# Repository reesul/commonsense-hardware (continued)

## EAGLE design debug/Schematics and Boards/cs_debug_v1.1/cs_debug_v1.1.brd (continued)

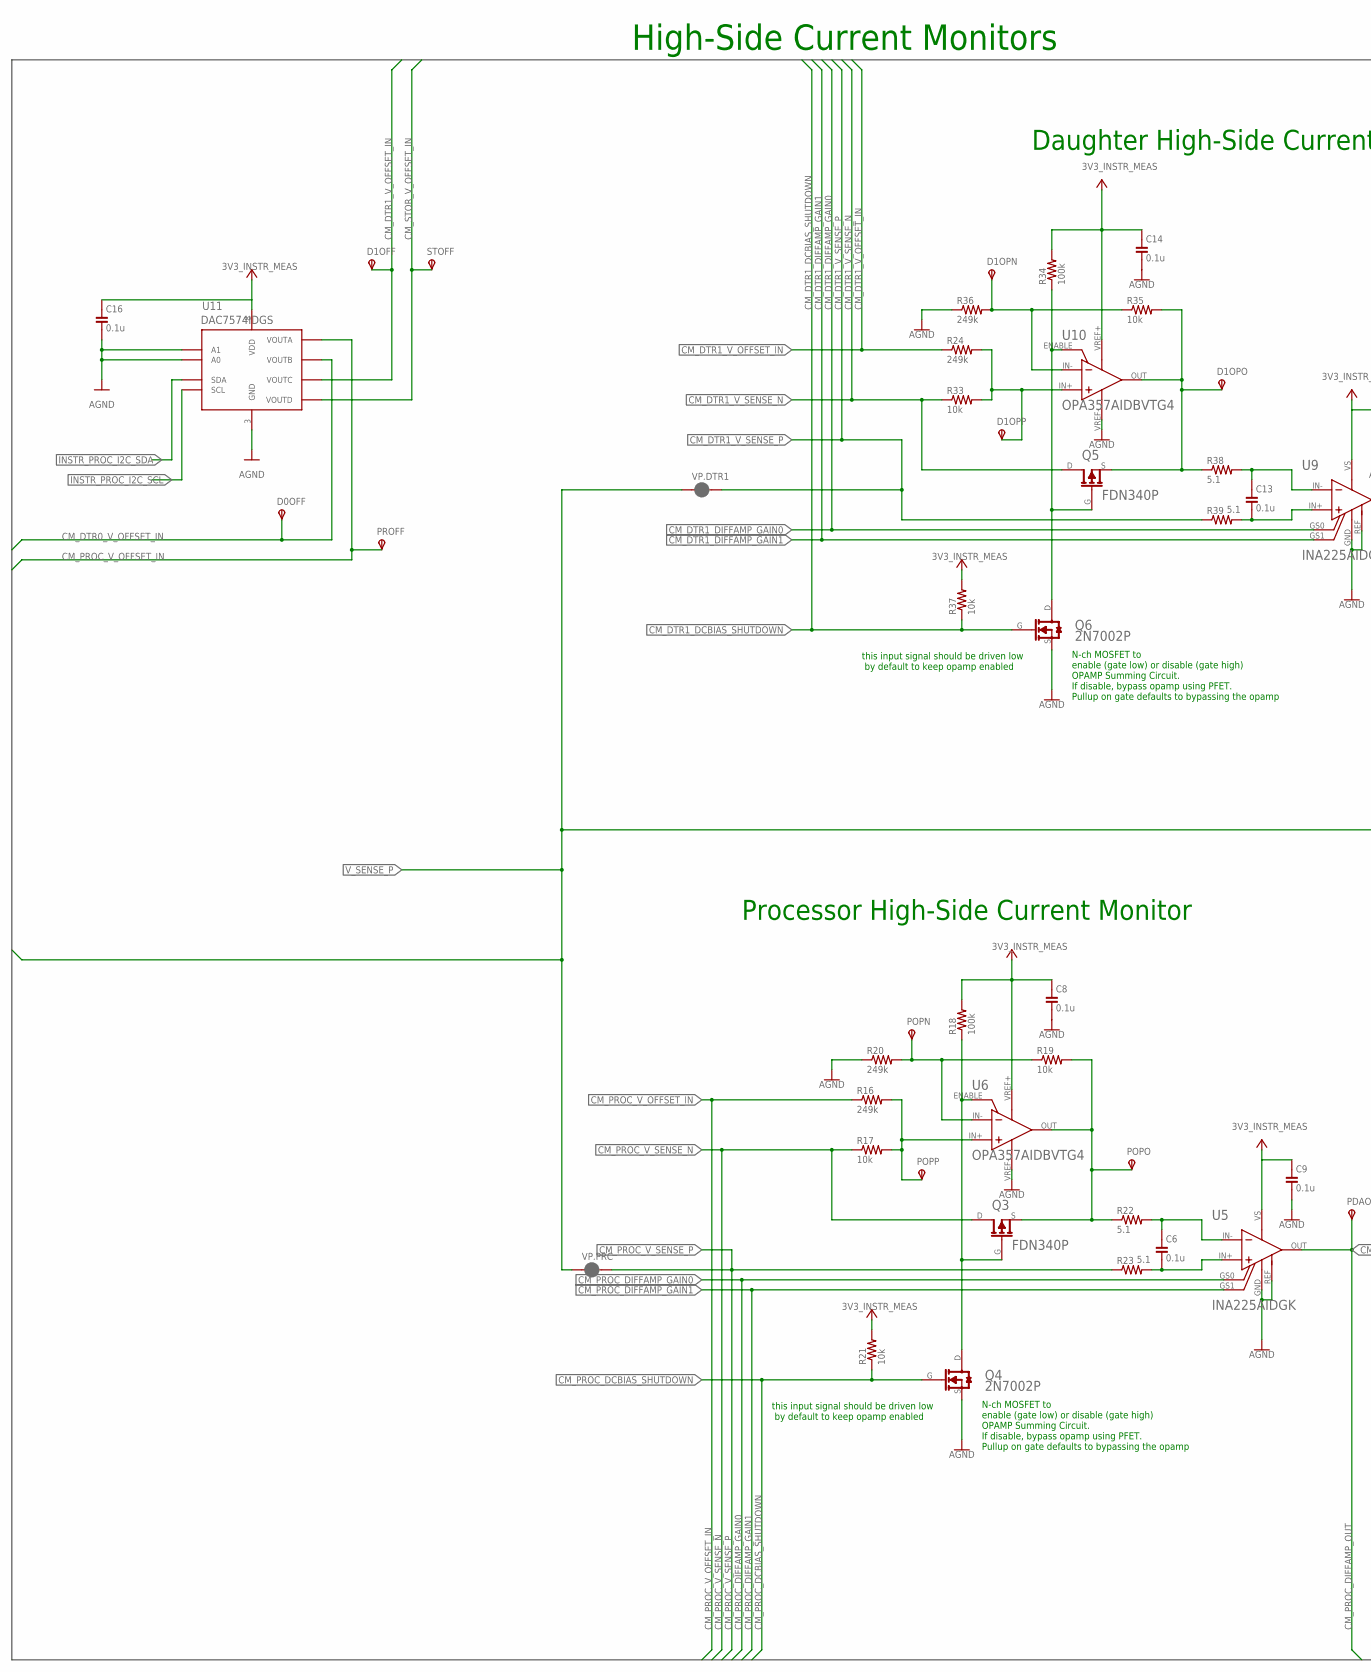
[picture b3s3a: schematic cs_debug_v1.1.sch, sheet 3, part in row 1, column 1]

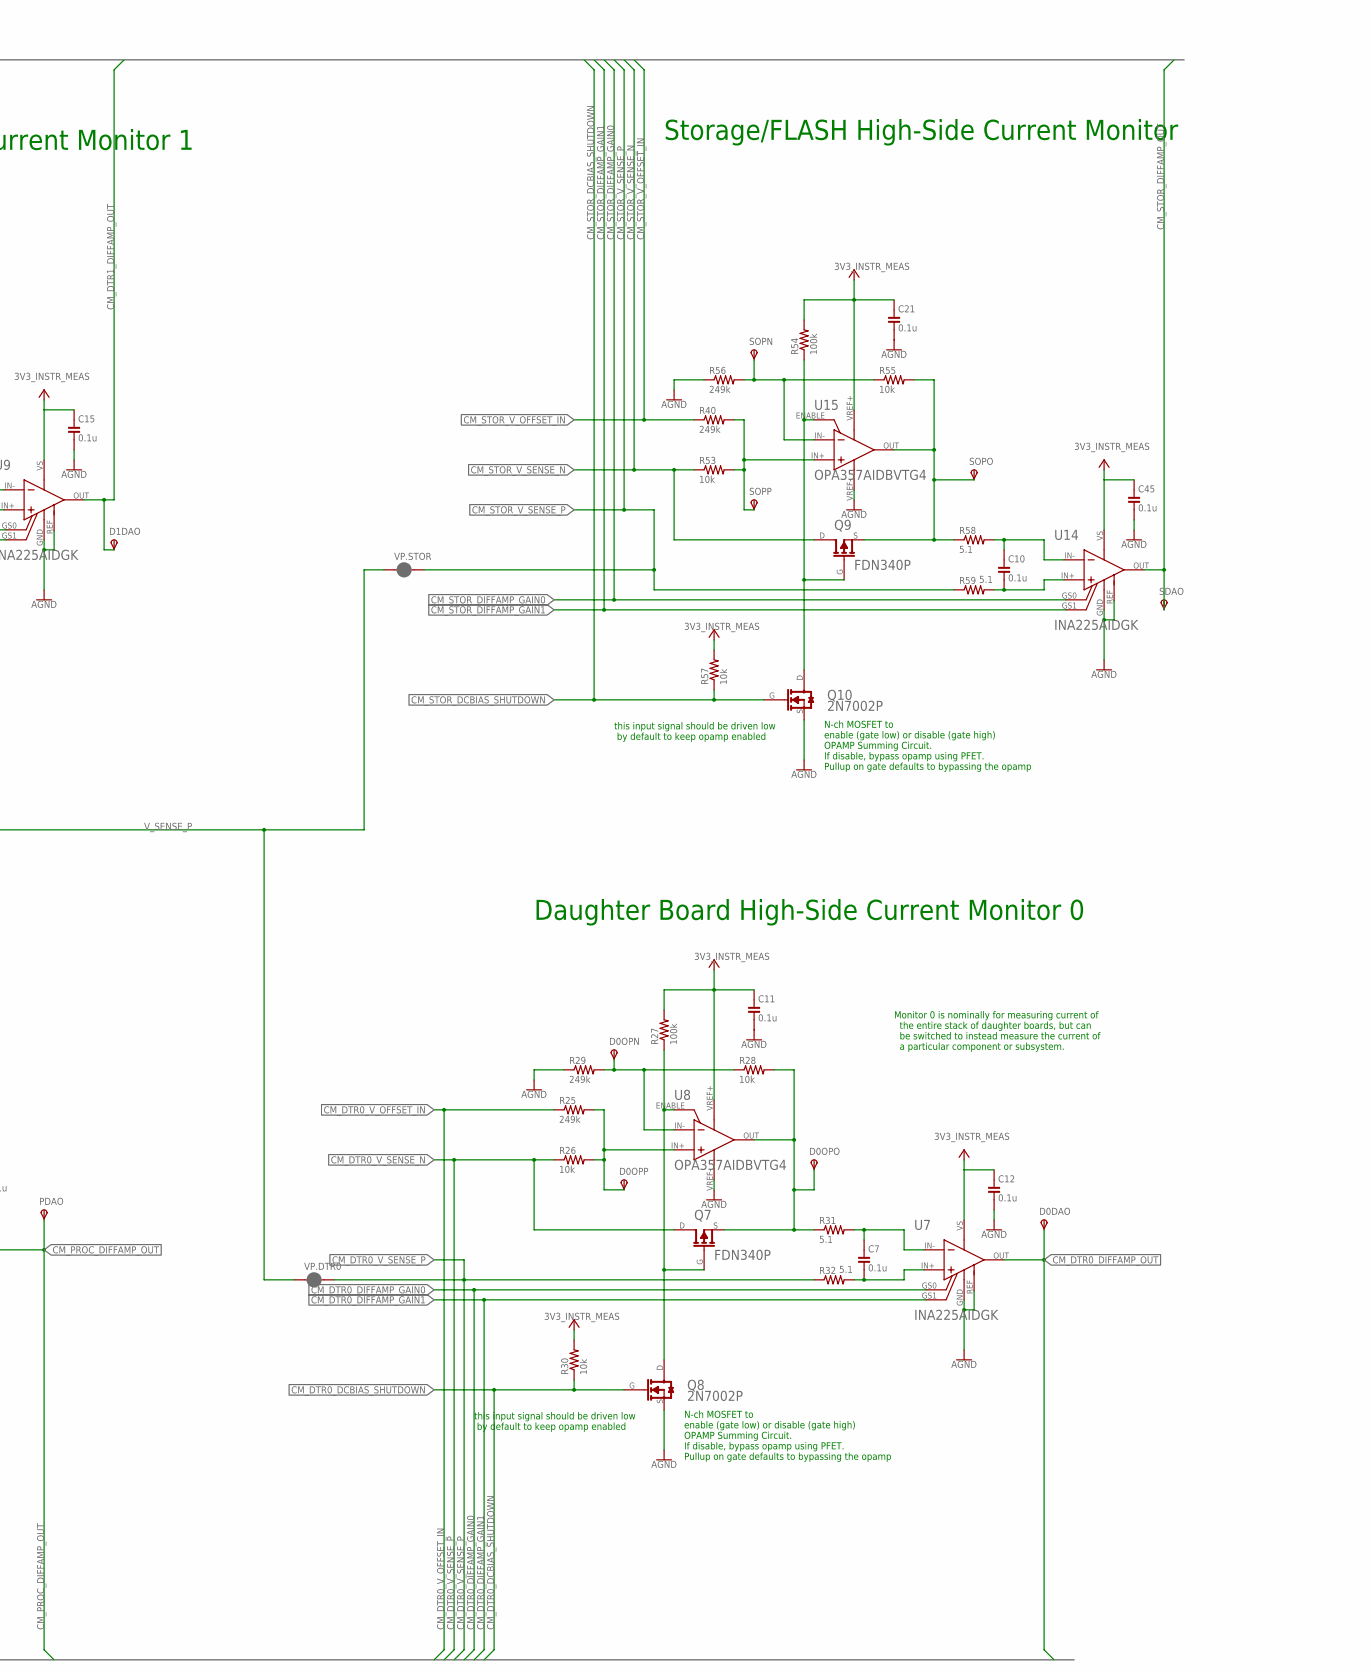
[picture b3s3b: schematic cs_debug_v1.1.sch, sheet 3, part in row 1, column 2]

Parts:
C6, C7, C10, C13: 0.1u; C0402; VOLTAGE 10V; MPN C0402C104K4RAC7411
C8, C9, C11, C12, C14, C15, C16, C21, C45: 0.1u; C0402; VOLTAGE 10V; MPN C0402C104K8RACTU
D0DAO, D0OFF, D0OPN, D0OPO, D0OPP, D1DAO, D1OFF, D1OPN, D1OPO, D1OPP: TPSTP10SQ; TP10SQ
PDAO: TPSTP10SQ; TP10SQ
POPN: TPSTP10SQ; TP10SQ
POPO: TPSTP10SQ; TP10SQ
POPP: TPSTP10SQ; TP10SQ
PROFF: TPSTP10SQ; TP10SQ
Q3, Q5, Q7, Q9: FDN340P; SOT23-3_FDN340P; PART_NO FDN340P
Q4, Q6, Q8, Q10: 2N7002P; SOT23-3_2N7002P; MPN 2N7002P,215
R16, R20, R24, R25, R29, R36, R40, R56: 249k; R0603; MPN ERA-3AEB2493V
R17, R19, R26, R28, R33, R35, R53, R55: 10k; R0402; MPN ERA-2AEB103X
R18, R27, R34, R54: 100k; R0402; MPN ERJ-2RKF1003X
R21, R30, R37, R57: 10k; R0402; MPN ERJ-2RKF1002X
R22, R23, R31, R32, R38, R39, R58: 5.1; R0603; MPN ERJ-U03F5R10V
R59: 5.1; R0603; MPN ERJ-3BQF5R1V
SDAO: TPSTP10SQ; TP10SQ
SOPN: TPSTP10SQ; TP10SQ
SOPO: TPSTP10SQ; TP10SQ
SOPP: TPSTP10SQ; TP10SQ
STOFF: TPSTP10SQ; TP10SQ
U5, U7, U9, U14: INA225AIDGK; DGK-MSOP8_INA225; MPN INA225AIDGKT
U6, U8, U10, U15: OPA357AIDBVTG4; PART_NO OPA357AIDBVTG4
U11: DAC7574IDGS; DGS10; MPN DAC7574IDGS
VP.DTR0, VP.DTR1, VP.PRC, VP.STOR: JUMPER-SMT_2_NC_PASTE_NO-SILK; SMT-JUMPER_2_NC_PASTE_NO-SILK

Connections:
3V3_INSTR_MEAS: C8.1, C9.1, C11.1, C12.1, C14.1, C15.1, C16.1, C21.1, C45.1, R18.2, R21.2, R27.2, R30.2, R34.2, R37.2, R54.2, R57.2, U5.VS (V+), U6.VREF+ (V+), U7.VS (V+), U8.VREF+ (V+), U9.VS (V+), U10.VREF+ (V+), U11.8 (VDD), U14.VS (V+), U15.VREF+ (V+); also elsewhere on the board
AGND: C8.2, C9.2, C11.2, C12.2, C14.2, C15.2, C16.2, C21.2, C45.2, Q4.S (SOURCE), Q6.S (SOURCE), Q8.S (SOURCE), Q10.S (SOURCE), R20.1, R29.1, R36.1, R56.1, U5.GND (V-), U5.REF, U6.VREF- (V-), U7.GND (V-), U7.REF, U8.VREF- (V-), U9.GND (V-), U9.REF, U10.VREF- (V-), U11.3 (GND), U11.9 (A0), U11.10 (A1), U14.GND (V-), U14.REF, U15.VREF- (V-); also elsewhere on the board
CM_DIFFAMP_N4: C6.1, R22.2, U5.IN-
CM_DIFFAMP_P4: C6.2, R23.2, U5.IN+
CM_DTR0_DCBIAS_SHUTDOWN: Q8.G (GATE), R30.1; also elsewhere on the board
CM_DTR0_DIFFAMP_GAIN0: U7.GS0; also elsewhere on the board
CM_DTR0_DIFFAMP_GAIN1: U7.GS1; also elsewhere on the board
CM_DTR0_DIFFAMP_N: C7.1, R31.2, U7.IN-
CM_DTR0_DIFFAMP_OUT: D0DAO.TP, U7.OUT; also elsewhere on the board
CM_DTR0_DIFFAMP_P3: C7.2, R32.2, U7.IN+
CM_DTR0_OPAMP_ENABLE: Q7.G, Q8.D (DRAIN), R27.1, U8.ENABLE
CM_DTR0_OPAMP_N: D0OPN.TP, R28.1, R29.2, U8.IN-
CM_DTR0_OPAMP_OUT: D0OPO.TP, Q7.S, R28.2, R31.1, U8.OUT
CM_DTR0_V_OFFSET_IN: D0OFF.TP, R25.1, U11.2 (VOUTB)
CM_DTR0_V_SENSE_N: Q7.D, R26.1; also elsewhere on the board
CM_DTR0_V_SENSE_P: R32.1, VP.DTR0.2
CM_DTR1_DCBIAS_SHUTDOWN: Q6.G (GATE), R37.1; also elsewhere on the board
CM_DTR1_DIFFAMP_GAIN0: U9.GS0; also elsewhere on the board
CM_DTR1_DIFFAMP_GAIN1: U9.GS1; also elsewhere on the board
CM_DTR1_DIFFAMP_N: C13.1, R38.2, U9.IN-
CM_DTR1_DIFFAMP_OUT: D1DAO.TP, U9.OUT; also elsewhere on the board
CM_DTR1_DIFFAMP_P: C13.2, R39.2, U9.IN+
CM_DTR1_OPAMP_N: D1OPN.TP, R35.1, R36.2, U10.IN-
CM_DTR1_OPAMP_OUT: D1OPO.TP, Q5.S, R35.2, R38.1, U10.OUT
CM_DTR1_OPAMP_P: D1OPP.TP, R24.2, R33.2, U10.IN+
CM_DTR1_V_OFFSET_IN: D1OFF.TP, R24.1, U11.4 (VOUTC)
CM_DTR1_V_SENSE_N: Q5.D, R33.1; also elsewhere on the board
CM_DTR1_V_SENSE_P: R39.1, VP.DTR1.2
CM_DTR_OPAMP_ENABLE: Q5.G, Q6.D (DRAIN), R34.1, U10.ENABLE
CM_OPAMP_ENABLE4: Q3.G, Q4.D (DRAIN), R18.1, U6.ENABLE
CM_OPAMP_N4: POPN.TP, R19.1, R20.2, U6.IN-
CM_OPAMP_OUT4: POPO.TP, Q3.S, R19.2, R22.1, U6.OUT
CM_OPAMP_P1: R40.2, R53.2, SOPP.TP, U15.IN+
CM_OPAMP_P3: D0OPP.TP, R25.2, R26.2, U8.IN+
CM_OPAMP_P4: POPP.TP, R16.2, R17.2, U6.IN+
CM_PROC_DCBIAS_SHUTDOWN: Q4.G (GATE), R21.1; also elsewhere on the board
CM_PROC_DIFFAMP_GAIN0: U5.GS0; also elsewhere on the board
CM_PROC_DIFFAMP_GAIN1: U5.GS1; also elsewhere on the board
CM_PROC_DIFFAMP_OUT: PDAO.TP, U5.OUT; also elsewhere on the board
CM_PROC_V_OFFSET_IN: PROFF.TP, R16.1, U11.1 (VOUTA)
CM_PROC_V_SENSE_N: Q3.D, R17.1; also elsewhere on the board
CM_PROC_V_SENSE_P: R23.1, VP.PRC.2
CM_STOR_DCBIAS_SHUTDOWN: Q10.G (GATE), R57.1; also elsewhere on the board
CM_STOR_DIFFAMP_GAIN0: U14.GS0; also elsewhere on the board
CM_STOR_DIFFAMP_GAIN1: U14.GS1; also elsewhere on the board
CM_STOR_DIFFAMP_N1: C10.1, R58.2, U14.IN-
CM_STOR_DIFFAMP_OUT: SDAO.TP, U14.OUT; also elsewhere on the board
CM_STOR_DIFFAMP_P1: C10.2, R59.2, U14.IN+
CM_STOR_OPAMP_ENABLE: Q9.G, Q10.D (DRAIN), R54.1, U15.ENABLE
CM_STOR_OPAMP_N: R55.1, R56.2, SOPN.TP, U15.IN-
CM_STOR_OPAMP_OUT: Q9.S, R55.2, R58.1, SOPO.TP, U15.OUT
CM_STOR_V_OFFSET_IN: R40.1, STOFF.TP, U11.5 (VOUTD)
CM_STOR_V_SENSE_N: Q9.D, R53.1; also elsewhere on the board
CM_STOR_V_SENSE_P: R59.1, VP.STOR.2
INSTR_PROC_I2C_SCL: U11.6 (SCL); also elsewhere on the board
INSTR_PROC_I2C_SDA: U11.7 (SDA); also elsewhere on the board
V_SENSE_P: VP.DTR0.1, VP.DTR1.1, VP.PRC.1, VP.STOR.1; also elsewhere on the board

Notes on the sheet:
High-Side Current Monitors
Storage/FLASH High-Side Current Monitor
this input signal should be driven low by default to keep opamp enabled
N-ch MOSFET to enable (gate low) or disable (gate high) OPAMP Summing Circuit. If disable, bypass opamp using PFET. Pullup on gate defaults to bypassing the opamp
Daughter High-Side Current Monitor 1
Daughter Board High-Side Current Monitor 0
Processor High-Side Current Monitor
Monitor 0 is nominally for measuring current of the entire stack of daughter boards, but can be switched to instead measure the current of a particular component or subsystem.

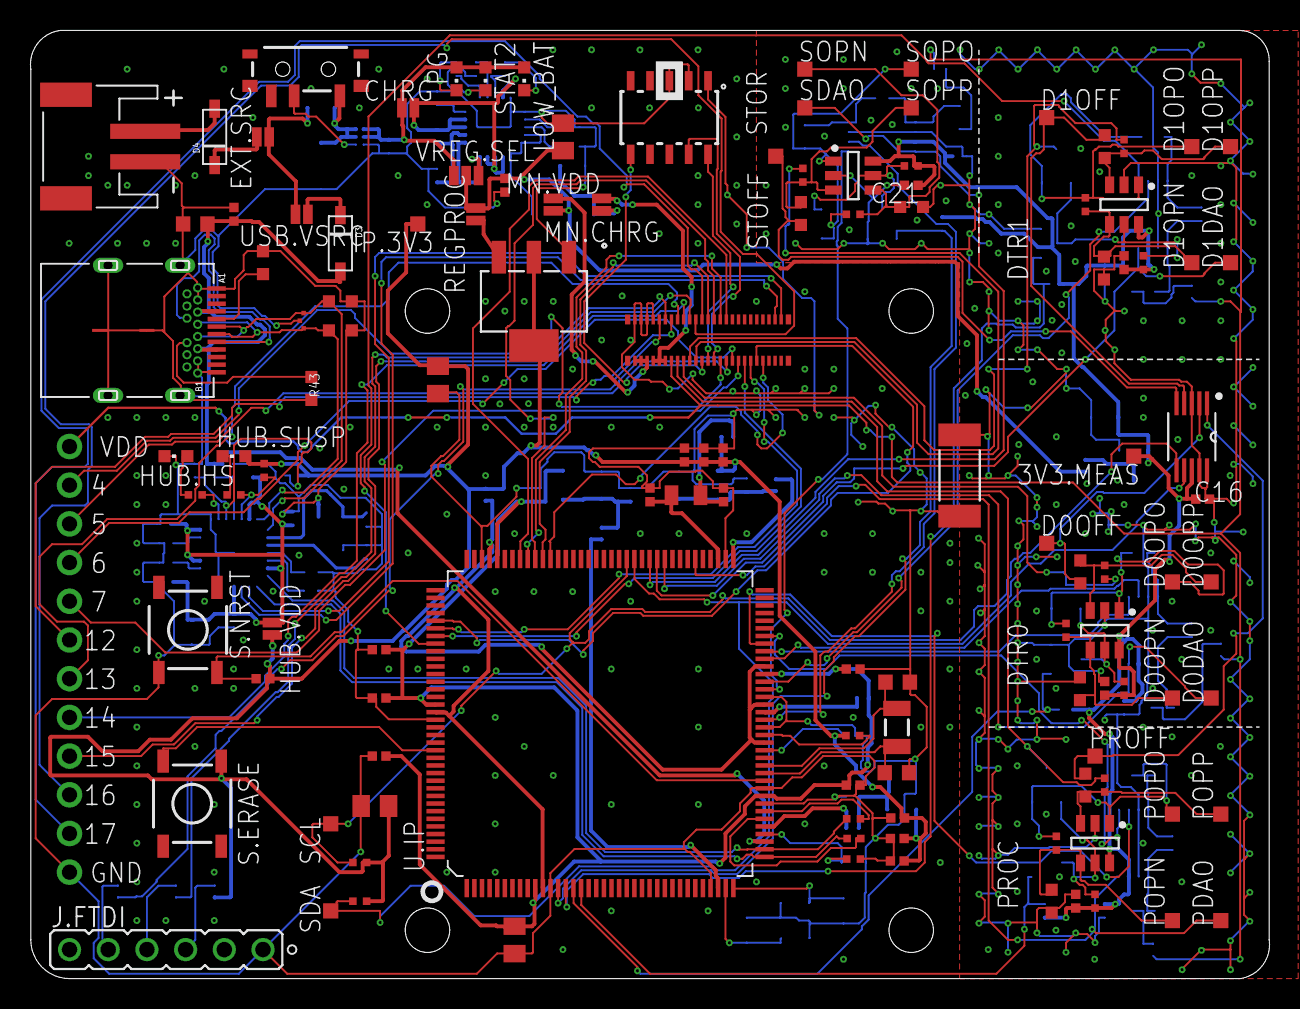
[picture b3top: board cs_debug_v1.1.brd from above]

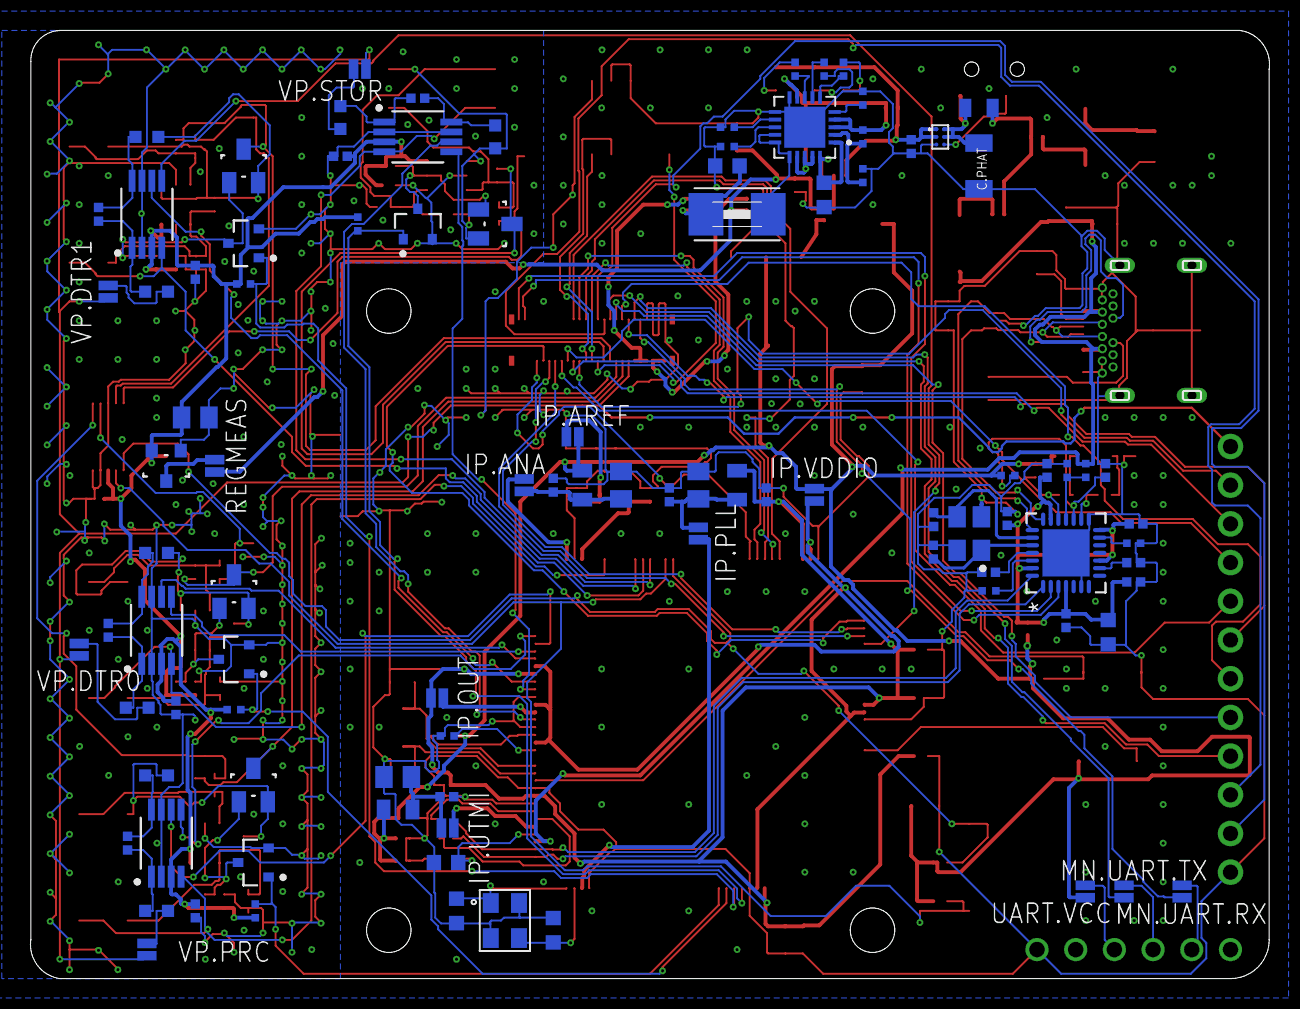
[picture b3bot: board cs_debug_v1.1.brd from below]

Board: 2 copper layers, 81.2 x 62.1 mm, 217 parts (97 on the bottom side), 156 nets.

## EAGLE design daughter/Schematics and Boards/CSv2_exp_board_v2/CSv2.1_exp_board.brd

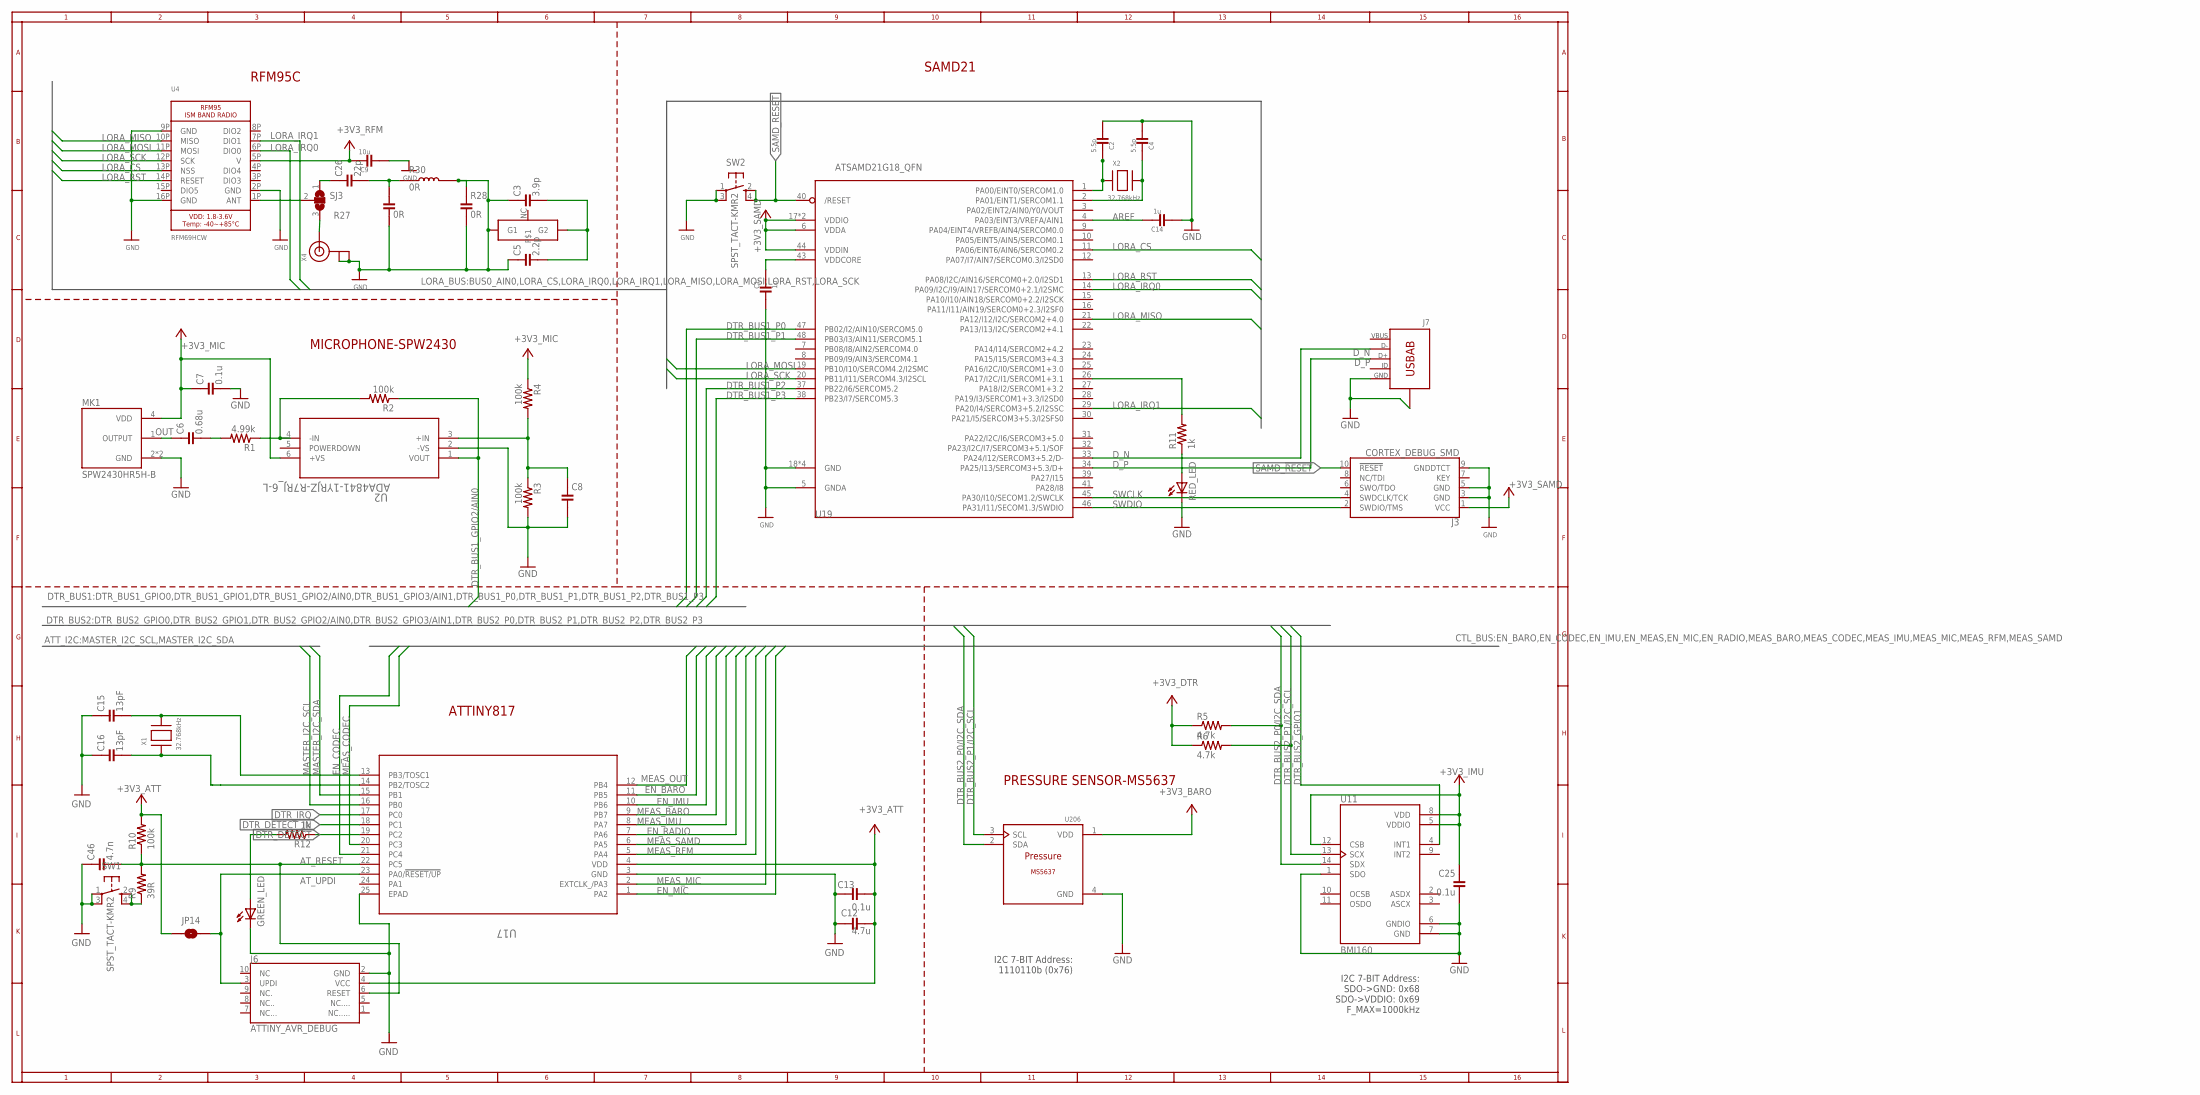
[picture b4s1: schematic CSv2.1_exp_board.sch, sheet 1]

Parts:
A1: ILA09_CHIP_ANTENNA; ILA_09_CHIP_ANTENNA; MPN ILA.09
C1, C8, C14: 1u; C0402; VOLTAGE 10V; MPN C0402C105M8PACTU
C2, C4: 5.5p; C0402; VOLTAGE 50V; MPN CBR04C559B5GAC
C3: 3.9p; C0402-S; VOLTAGE 50V; MPN GJM1555C1H3R9WB01D
C5: 2.2p; C0402-S; VOLTAGE 50V; MPN GJM1555C1H2R2WB01D
C6: 0.68u; C0402; MPN CC0402KRX5R5BB684
C7, C13, C25: 0.1u; C0402; VOLTAGE 16V; MPN C0402C104K4RACTU
C9: 10u; C0603; MPN GRM188R60J106KE47D
C12: 4.7u; C0603; VOLTAGE 10V; MPN C0603C475K8PACTU
C15, C16: 13pF; C0402; PARTNO *
C26: 22p; C0402-S; VOLTAGE 50V; MPN CBR04C220F5GAC
C46: 4.7n; C0402; VOLTAGE 25V; MPN C0402C472K3RACTU
GREEN_LED: LEDCHIPLED_0603; CHIPLED_0603; MPN APT1608SGC
J3: CORTEX_DEBUG_SMD; SAMTECH_FTSH-105-01; MPN FTSH-105-01-L-DV-K
J6: ATTINY_AVR_DEBUG; SAMTECH_FTSH-105-01; MPN FTSH-105-01-L-DV-K
J7: J-USB-HIROSE-MICRO-USB; USB-THRU-ZX62D-AB-5P8; PARTNO ZX62D-AB-5P8(30)
JP14: JUMPER-SMT_2_NO_PASTEFREE; SMT-JUMPER_2_NO_PASTEFREE_NO-SILK; PARTNO *
MK1: SPW2430HR5H-B; MIC_SPW2430HR5H-B; MPN SPW2430HR5H-B
R1: 4.99k; R0402; MPN ERA-2AEB4991X
R2, R3, R4: 100k; R0402; MPN RT0402BRD07100KL
R5, R6: 4.7k; R0402; MPN ERJ2RKF4701X
R9: 39R; R0402; MPN ERJ-2RKF39R0X
R10: 100k; R0402; MPN ERJ-2RKF1003X
R11, R12: 1k; R0402; MPN ERJ-2RKF1001X
R27, R28: 0R; C0402-S; MPN RMCF0402ZT0R00
R30: 0R; L0402; MPN RMCF0402ZT0R00
RED_LED: LEDCHIPLED_0603; CHIPLED_0603; MPN APT1608SURCK
SJ3: JUMPER_SJ2W; JUMPER_SJ_2
SW1, SW2: SPST_TACT-KMR2; KMR2; MPN KMR241NG ULC LFS
U2: ADA4841-1YRJZ-R7RJ_6-L; RJ_6-L; MPN ADA48411YRJZR7
U4: RFM69HCW; RFM-MOD; MPN RFM95CW
U11: BMI160; PQFN50P300X250X88-14N; MPN BMI160
U17: ATTINY817-MFRQFN24_RX4MC-L_ATTINY817-MFR; ATTINY817-MFRQFN24_RX4MC-L_QFN24_4X4MC; MPN ATTINY817MFR
U19: ATSAMD21G18_QFN; MICROBUILDER_TQFN48_7MM; MPN ATSAMD21G18A-MF
U206: MS5637
X1: 32.768kHz; ADAFRUIT2_XTAL3215; PARTNO *
X2: 32.768kHz; ADAFRUIT2_XTAL3215; MPN NX3215SA-32.768K-STD-MUA-14
X4: uFL; U.FL; MPN U.FL-R-SMT-1(01)

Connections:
+3V3_ATT: C12.2, C13.2, J6.4 (VCC), JP14.1, R10.2, U17.4 (VDD); also elsewhere on the board
+3V3_BARO: U206.1 (VDD); also elsewhere on the board
+3V3_DTR: R5.1, R6.1; also elsewhere on the board
+3V3_IMU: C25.1, U11.5 (VDDIO), U11.8 (VDD), U11.12 (CSB); also elsewhere on the board
+3V3_MIC: C7.1, MK1.4 (VDD), R4.1, U2.6 (+VS); also elsewhere on the board
+3V3_RFM: C9.1, U4.5P (V); also elsewhere on the board
+3V3_SAMD: J3.1 (VCC), U19.6 (VDDA), U19.17 (VDDIO), U19.36 (VDDIO), U19.44 (VDDIN); also elsewhere on the board
AREF: C14.1, U19.4 (PA03/EINT3/VREFA/AIN1)
AT_RESET: C46.2, J6.6 (RESET), R9.2, R10.1, U17.22 (PC5)
AT_UPDI: J6.3 (UPDI), JP14.2, U17.23 (PA0/!RESET/UP)
DTR_BUS1_GPIO2/AIN0: R2.1, U2.1 (VOUT); also elsewhere on the board
DTR_BUS1_P0: U19.47 (PB02/I2/AIN10/SERCOM5.0); also elsewhere on the board
DTR_BUS1_P1: U19.48 (PB03/I3/AIN11/SERCOM5.1); also elsewhere on the board
DTR_BUS1_P2: U19.37 (PB22/I6/SERCOM5.2); also elsewhere on the board
DTR_BUS1_P3: U19.38 (PB23/I7/SERCOM5.3); also elsewhere on the board
DTR_BUS2_GPIO1: U11.4 (INT1); also elsewhere on the board
DTR_BUS2_P0/I2C_SDA: R5.2, U11.14 (SDX), U206.2 (SDA); also elsewhere on the board
DTR_BUS2_P1/I2C_SCL: R6.2, U11.13 (SCX), U206.3 (SCL); also elsewhere on the board
DTR_DETECT: R12.1, U17.19 (PC2); also elsewhere on the board
DTR_DETECT_IN: U17.18 (PC1)
DTR_DETECT_LED: GREEN_LED.A, R12.2
DTR_IRQ: U17.17 (PC0); also elsewhere on the board
D_N: J7.D-, U19.33 (PA24/I12/SERCOM3+5.2/D-)
D_P: J7.D+, U19.34 (PA25/I13/SERCOM3+5.3/D+)
EN_BARO: U17.11 (PB5); also elsewhere on the board
EN_CODEC: U17.21 (PC4); also elsewhere on the board
EN_IMU: U17.10 (PB6); also elsewhere on the board
EN_MIC: U17.1 (PA2); also elsewhere on the board
EN_RADIO: U17.7 (PA6); also elsewhere on the board
GND: A1.G1, C1.2, C2.2, C3.1, C4.2, C5.1, C7.2, C8.2, C9.2, C12.1, C13.1, C14.2, C15.1, C16.1, C25.2, C46.1, GREEN_LED.C, J3.3 (GND), J3.5 (GND), J3.9 (GNDDTCT), J6.2 (GND), J7.GND, J7.S1 (SHIELD), J7.S2 (SHIELD), J7.S3 (SHIELD), J7.S4 (SHIELD), MK1.2 (GND), MK1.3 (GND), R3.2, R27.2, R28.1, R28.2, R30.2, RED_LED.C, SW1.1, SW1.3 (P1), SW2.1, SW2.3 (P1), U2.2 (-VS), U4.2P (GND), U4.9P (GND), U4.16P (GND), U11.1 (SDO), U11.6 (GNDIO), U11.7 (GND), U17.3 (GND), U17.25 (EPAD), U19.5 (GNDA), U19.18 (GND), U19.35 (GND), U19.42 (GND), U19.THERMAL (GND), U206.4 (GND), X4.1 (GND), X4.2 (GND); also elsewhere on the board
IN-: R1.1, R2.2, U2.4 (-IN)
LORA_CS: U4.13P (NSS), U19.11 (PA06/EINT6/AIN6/SERCOM0.2)
LORA_IRQ0: U4.6P (DIO0), U19.14 (PA09/I2C/I9/AIN17/SERCOM0+2.1/I2SMC)
LORA_IRQ1: U4.7P (DIO1), U19.29 (PA20/I4/SERCOM3+5.2/I2SSC)
LORA_MISO: U4.10P (MISO), U19.21 (PA12/I12/I2C/SERCOM2+4.0)
LORA_MOSI: U4.11P (MOSI), U19.19 (PB10/I10/SERCOM4.2/I2SMC)
LORA_RST: U4.14P (RESET), U19.13 (PA08/I2C/AIN16/SERCOM0+2.0/I2SD1)
LORA_SCK: U4.12P (SCK), U19.20 (PB11/I11/SERCOM4.3/I2SCL)
MASTER_I2C_SCL: U17.16 (PB0); also elsewhere on the board
MASTER_I2C_SDA: U17.15 (PB1); also elsewhere on the board
MEAS_BARO: U17.9 (PB7); also elsewhere on the board
MEAS_CODEC: U17.20 (PC3); also elsewhere on the board
MEAS_IMU: U17.8 (PA7); also elsewhere on the board
MEAS_MIC: U17.2 (EXTCLK_/PA3); also elsewhere on the board
MEAS_OUT: U17.12 (PB4); also elsewhere on the board
MEAS_RFM: U17.5 (PA4); also elsewhere on the board
MEAS_SAMD: U17.6 (PA5); also elsewhere on the board
unnamed: C1.1, U19.43 (VDDCORE)
unnamed: SJ3.3, X4.3 (SIGNAL)
unnamed: C8.1, R3.1, R4.2, U2.3 (+IN)
unnamed: A1.G2, C3.2, C5.2
unnamed: C2.1, U19.1 (PA00/EINT0/SERCOM1.0), X2.P$1
unnamed: C6.2, R1.2
unnamed: C4.1, U19.2 (PA01/EINT1/SERCOM1.1), X2.P$2
unnamed: C26.1, SJ3.1
unnamed: R9.1, SW1.2 (S), SW1.4 (S1)
unnamed: C26.2, R27.1, R30.1
unnamed: R11.2, U19.26 (PA17/I2C/I1/SERCOM1+3.1)
unnamed: R11.1, RED_LED.A
unnamed: C16.2, U17.14 (PB2/TOSC2), X1.P$1
unnamed: C15.2, U17.13 (PB3/TOSC1), X1.P$2
unnamed: SJ3.2, U4.1P (ANT)
OUT: C6.1, MK1.1 (OUTPUT)
POWERDOWN: U2.5 (POWERDOWN)
SAMD_!RESET: J3.10 (!RESET), SW2.2 (S), SW2.4 (S1), U19.40 (/RESET)
SWCLK: J3.4 (SWDCLK/TCK), U19.45 (PA30/I10/SECOM1.2/SWCLK)
SWDIO: J3.2 (SWDIO/TMS), U19.46 (PA31/I11/SECOM1.3/SWDIO)

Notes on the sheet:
RFM95C
SAMD21
ATTINY817
MICROPHONE-SPW2430
PRESSURE SENSOR-MS5637
I2C 7-BIT Address: SDO->GND: 0x68 SDO->VDDIO: 0x69 F_MAX=1000kHz
I2C 7-BIT Address: 1110110b (0x76)

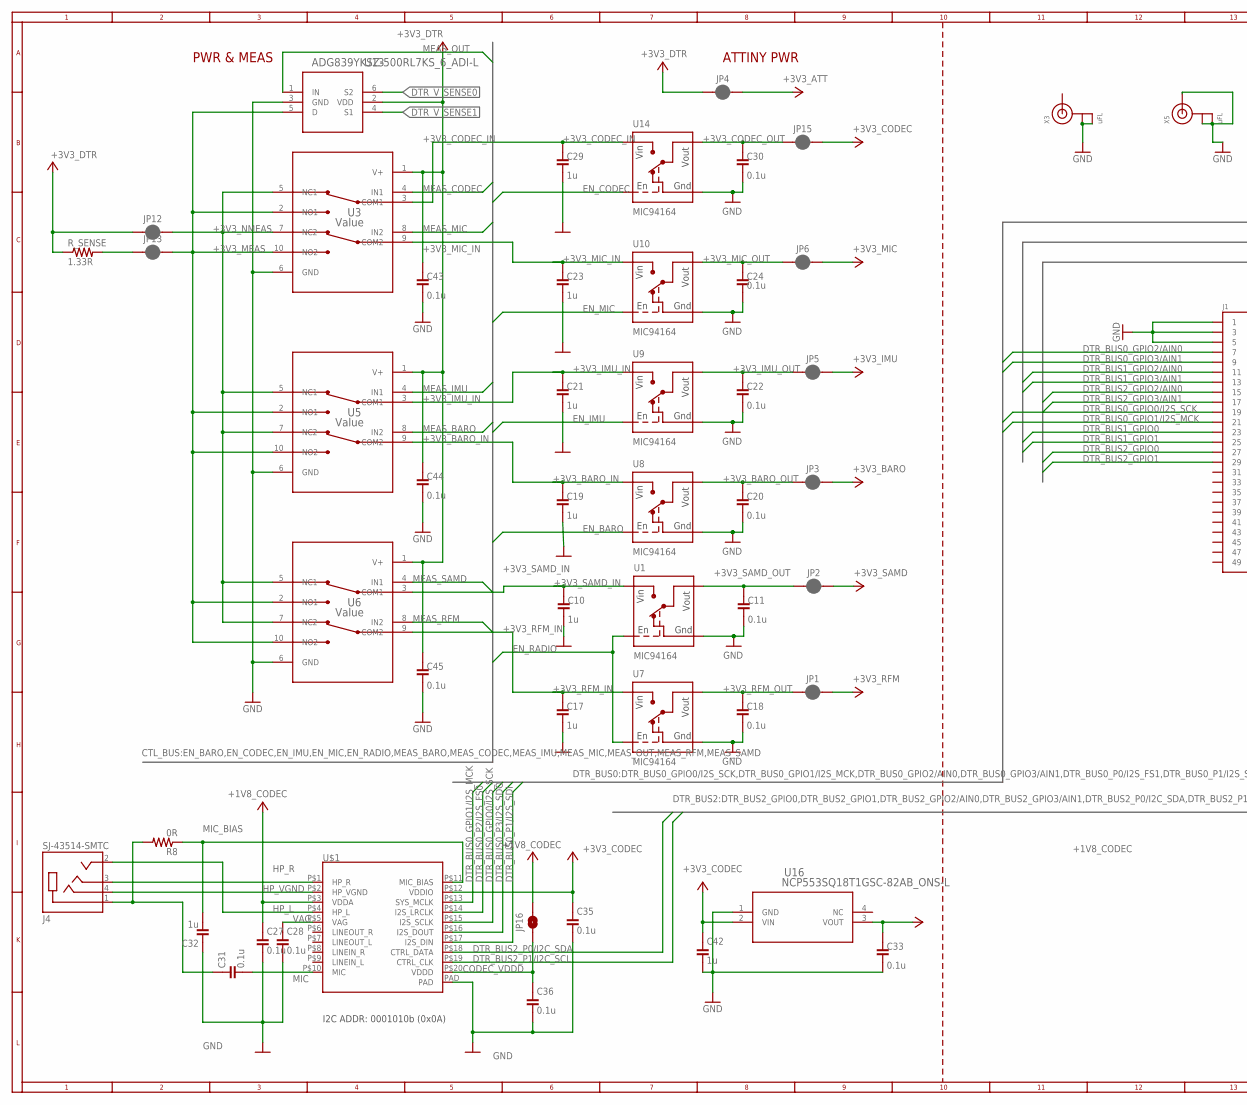
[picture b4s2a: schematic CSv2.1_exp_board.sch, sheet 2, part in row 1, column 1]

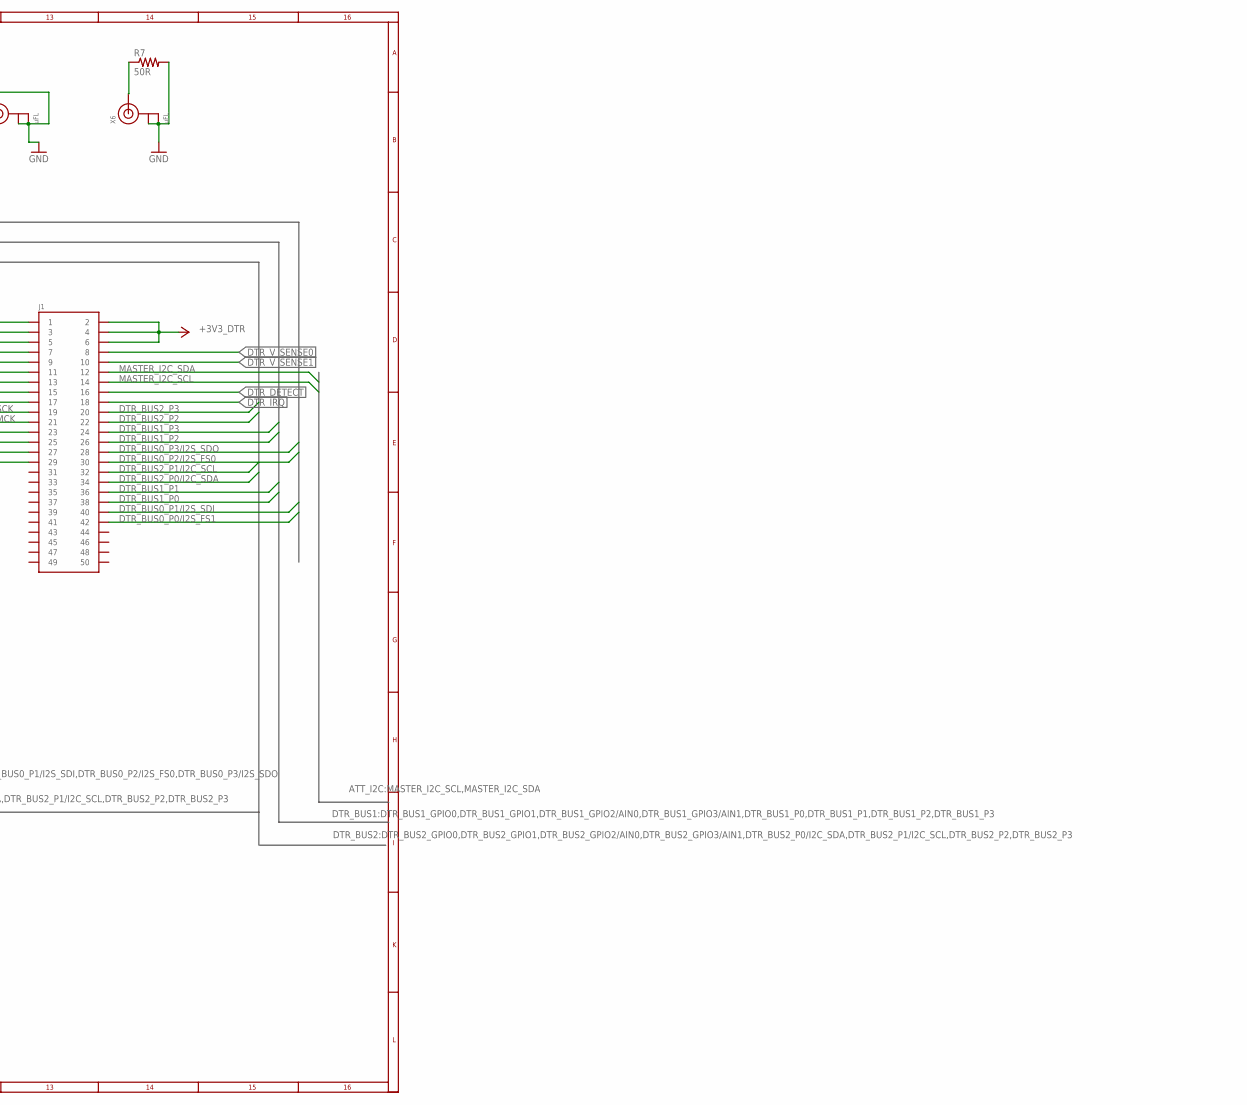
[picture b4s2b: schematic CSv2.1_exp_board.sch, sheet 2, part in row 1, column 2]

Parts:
C10, C17, C19, C21, C23, C29: 1u; C0402; MPN CC0402KRX5R5BB105
C11, C18, C20, C22, C24, C27, C28, C30, C31, C33, C35, C36, C43, C44, C45: 0.1u; C0402; MPN CC0402KRX7R6BB104
C32: 1u; C0402; MPN C1005X7S1A105K050BC
C42: 1u; C0402; VOLTAGE 10V; MPN C1005X7S1A105K050BC
J1: HIROSE-DF40_50-PIN_CONNECTORS-HEADER; HRS_DF40C-50DP-0.4V(51); MPN DF40C-50DP-0.4V(51)
J4: SJ-43514-SMTC; CUI_SJ-43514-SMT-TEMP; MPN SJ-43514-SMT
JP1, JP2, JP3, JP4, JP5, JP6, JP12, JP13, JP15: JUMPER-SMT_2_NC_PASTELG_NO-SILK; SMT-JUMPER_2_NC_PASTE_NO-SILK
JP16: JUMPER-SMT_2_NO_PASTEFREE; SMT-JUMPER_2_NO_PASTEFREE_NO-SILK
R7: 50R; R0402; MPN FC0402E50R0BST1
R8: 0R; R0402; MPN RMCF0402ZT0R00
R_SENSE: 1.33R; R0402; MPN CRCW04021R33FKED
U1, U7, U8, U9, U10, U14: LOADSWITCH-MIC94164; WLCSP6_2X3; PARTNO MIC94164YCS-TR
U3, U5, U6: Value; DGS0010A_L; MPN TS3A24159DGSR
U13: ADG839YKSZ-500RL7KS_6_ADI-L; KS_6_ADI-L; MPN ADG839YKSZ-500RL7
U16: NCP553SQ18T1GSC-82AB_ONS-L; SC-82AB_ONS-L; MPN NCP553SQ18T1G
U$1: SGTL5000-QFN20; MPN SGTL5000XNLA3R2
X3, X5, X6: uFL; U.FL; MPN U.FL-R-SMT-1(01)

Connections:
+1V8_CODEC: C27.1, C33.1, JP16.2, U16.3 (VOUT), U$1.P$3 (VDDA)
+3V3_ATT: JP4.2; also elsewhere on the board
+3V3_BARO: JP3.2; also elsewhere on the board
+3V3_BARO_IN: C19.1, U5.9 (COM2), U8.A2 (VIN), U8.B2 (VIN)
+3V3_BARO_OUT: C20.1, JP3.1, U8.A1 (VOUT), U8.B1 (VOUT)
+3V3_CODEC: C35.1, C42.1, JP15.2, U16.2 (VIN), U$1.P$12 (VDDIO)
+3V3_CODEC_IN: C29.1, U3.3 (COM1), U14.A2 (VIN), U14.B2 (VIN)
+3V3_CODEC_OUT: C30.1, JP15.1, U14.A1 (VOUT), U14.B1 (VOUT)
+3V3_DTR: C43.1, C44.1, C45.1, J1.2, J1.4, J1.6, JP4.1, JP12.1, R_SENSE.1, U3.1 (V+), U5.1 (V+), U6.1 (V+), U13.2 (VDD); also elsewhere on the board
+3V3_IMU: JP5.2; also elsewhere on the board
+3V3_IMU_IN: C21.1, U5.3 (COM1), U9.A2 (VIN), U9.B2 (VIN)
+3V3_IMU_OUT: C22.1, JP5.1, U9.A1 (VOUT), U9.B1 (VOUT)
+3V3_MEAS: JP13.2, U3.2 (NO1), U3.10 (NO2), U5.2 (NO1), U5.10 (NO2), U6.2 (NO1), U6.10 (NO2), U13.5 (D)
+3V3_MIC: JP6.2; also elsewhere on the board
+3V3_MIC_IN: C23.1, U3.9 (COM2), U10.A2 (VIN), U10.B2 (VIN)
+3V3_MIC_OUT: C24.1, JP6.1, U10.A1 (VOUT), U10.B1 (VOUT)
+3V3_NMEAS: JP12.2, U3.5 (NC1), U3.7 (NC2), U5.5 (NC1), U5.7 (NC2), U6.5 (NC1), U6.7 (NC2)
+3V3_RFM: JP1.2; also elsewhere on the board
+3V3_RFM_IN: C17.1, U6.9 (COM2), U7.A2 (VIN), U7.B2 (VIN)
+3V3_RFM_OUT: C18.1, JP1.1, U7.A1 (VOUT), U7.B1 (VOUT)
+3V3_SAMD: JP2.2; also elsewhere on the board
+3V3_SAMD_IN: C10.1, U1.A2 (VIN), U1.B2 (VIN), U6.3 (COM1)
+3V3_SAMD_OUT: C11.1, JP2.1, U1.A1 (VOUT), U1.B1 (VOUT)
CODEC_VDDD: C36.1, JP16.1, U$1.P$20 (VDDD)
DTR_BUS0_GPIO0/I2S_SCK: J1.19, U$1.P$15 (I2S_SCLK)
DTR_BUS0_GPIO1/I2S_MCK: J1.21, U$1.P$13 (SYS_MCLK)
DTR_BUS0_GPIO2/AIN0: J1.7
DTR_BUS0_GPIO3/AIN1: J1.9
DTR_BUS0_P0/I2S_FS1: J1.42
DTR_BUS0_P1/I2S_SDI: J1.40, U$1.P$17 (I2S_DIN)
DTR_BUS0_P2/I2S_FS0: J1.30, U$1.P$14 (I2S_LRCLK)
DTR_BUS0_P3/I2S_SDO: J1.28, U$1.P$16 (I2S_DOUT)
DTR_BUS1_GPIO0: J1.23
DTR_BUS1_GPIO1: J1.25
DTR_BUS1_GPIO2/AIN0: J1.11; also elsewhere on the board
DTR_BUS1_GPIO3/AIN1: J1.13
DTR_BUS1_P0: J1.38; also elsewhere on the board
DTR_BUS1_P1: J1.36; also elsewhere on the board
DTR_BUS1_P2: J1.26; also elsewhere on the board
DTR_BUS1_P3: J1.24; also elsewhere on the board
DTR_BUS2_GPIO0: J1.27
DTR_BUS2_GPIO1: J1.29; also elsewhere on the board
DTR_BUS2_GPIO2/AIN0: J1.15
DTR_BUS2_GPIO3/AIN1: J1.17
DTR_BUS2_P0/I2C_SDA: J1.34, U$1.P$18 (CTRL_DATA); also elsewhere on the board
DTR_BUS2_P1/I2C_SCL: J1.32, U$1.P$19 (CTRL_CLK); also elsewhere on the board
DTR_BUS2_P2: J1.22
DTR_BUS2_P3: J1.20
DTR_DETECT: J1.16; also elsewhere on the board
DTR_IRQ: J1.18; also elsewhere on the board
DTR_V_SENSE0: J1.8, U13.6 (S2)
DTR_V_SENSE1: J1.10, U13.4 (S1)
EN_BARO: U8.C2 (ENABLE); also elsewhere on the board
EN_CODEC: U14.C2 (ENABLE); also elsewhere on the board
EN_IMU: U9.C2 (ENABLE); also elsewhere on the board
EN_MIC: U10.C2 (ENABLE); also elsewhere on the board
EN_RADIO: U1.C2 (ENABLE), U7.C2 (ENABLE); also elsewhere on the board
GND: C10.2, C11.2, C17.2, C18.2, C19.2, C20.2, C21.2, C22.2, C23.2, C24.2, C27.2, C28.2, C29.2, C30.2, C32.1, C33.2, C35.2, C36.2, C42.2, C43.2, C44.2, C45.2, J1.1, J1.3, J1.5, R7.2, U1.C1 (GND), U3.6 (GND), U5.6 (GND), U6.6 (GND), U7.C1 (GND), U8.C1 (GND), U9.C1 (GND), U10.C1 (GND), U13.3 (GND), U14.C1 (GND), U16.1 (GND), U$1.PAD, X3.1 (GND), X3.2 (GND), X5.1 (GND), X5.2 (GND), X5.3 (SIGNAL), X6.1 (GND), X6.2 (GND); also elsewhere on the board
HP_L: J4.2 (TIP), U$1.P$4 (HP_L)
HP_R: J4.3 (RING1), U$1.P$1 (HP_R)
HP_VGND: J4.4 (RING2), U$1.P$2 (HP_VGND)
MASTER_I2C_SCL: J1.14; also elsewhere on the board
MASTER_I2C_SDA: J1.12; also elsewhere on the board
MEAS_BARO: U5.8 (IN2); also elsewhere on the board
MEAS_CODEC: U3.4 (IN1); also elsewhere on the board
MEAS_IMU: U5.4 (IN1); also elsewhere on the board
MEAS_MIC: U3.8 (IN2); also elsewhere on the board
MEAS_OUT: U13.1 (IN); also elsewhere on the board
MEAS_RFM: U6.8 (IN2); also elsewhere on the board
MEAS_SAMD: U6.4 (IN1); also elsewhere on the board
MIC: C31.2, U$1.P$10 (MIC)
MIC_BIAS: C32.2, R8.1, U$1.P$11 (MIC_BIAS)
unnamed: JP13.1, R_SENSE.2
unnamed: R7.1, X6.3 (SIGNAL)
unnamed: C31.1, J4.1 (SLEEVE), R8.2
VAG: C28.1, U$1.P$5 (VAG)

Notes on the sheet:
PWR & MEAS
ATTINY PWR
I2C ADDR: 0001010b (0x0A)
